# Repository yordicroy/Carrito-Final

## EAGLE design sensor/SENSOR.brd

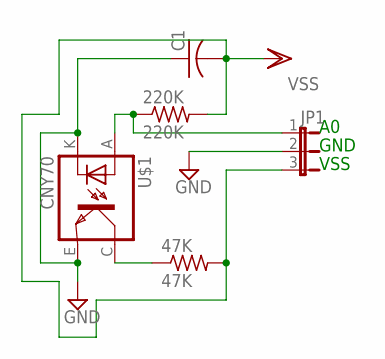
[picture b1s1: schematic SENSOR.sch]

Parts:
47K: 47K; 0309/12
220K: 220K; 0309/12
C1: C-US025-030X050; C025-030X050
JP1: JP2E; JP2
U$1: CNY70; 4

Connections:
GND: C1.1, JP1.2, U$1.E (EMI), U$1.K (C)
unnamed: 220K.1, JP1.1, U$1.A
unnamed: 47K.1, U$1.C (COL)
VSS: 47K.2, 220K.2, C1.2, JP1.3

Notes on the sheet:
GND
VSS

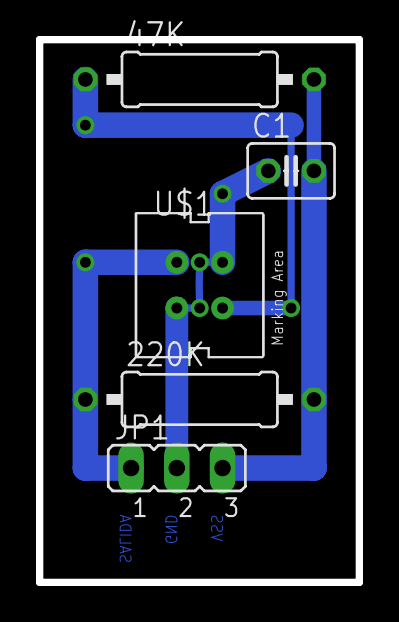
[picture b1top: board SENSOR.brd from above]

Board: 2 copper layers, 17.8 x 30.2 mm, 5 parts (0 on the bottom side), 4 nets.

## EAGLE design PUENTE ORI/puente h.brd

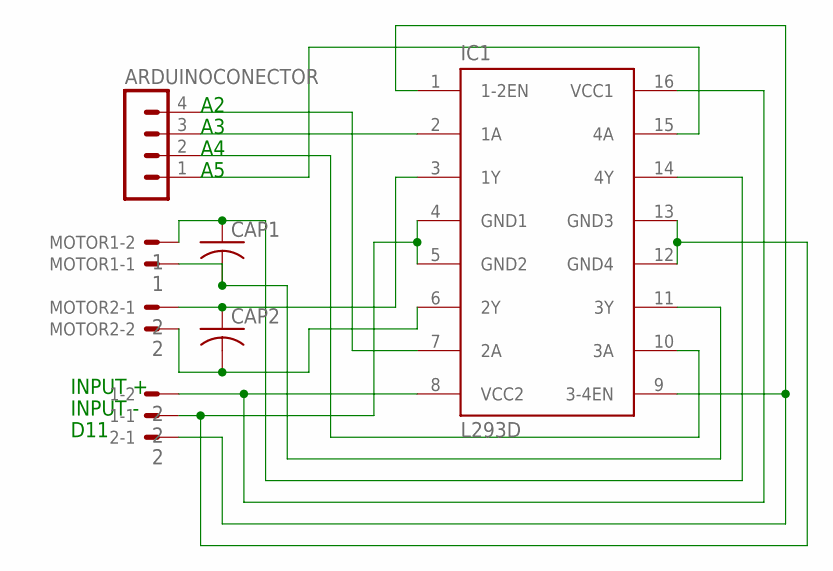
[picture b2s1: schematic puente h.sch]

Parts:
1, 2: 2; 332-02
ARDUINOCONECTOR: MA04-1
CAP1, CAP2: C-US025-025X050; C025-025X050
IC1: L293D; DIL16
MOTOR1: 1; 332-02
MOTOR2: 2; 332-02

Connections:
unnamed: ARDUINOCONECTOR.4, IC1.7 (2A)
unnamed: ARDUINOCONECTOR.3, IC1.2 (1A)
unnamed: ARDUINOCONECTOR.2, IC1.10 (3A)
unnamed: ARDUINOCONECTOR.1, IC1.15 (4A)
unnamed: CAP1.2, IC1.11 (3Y), MOTOR1.1
unnamed: CAP1.1, IC1.14 (4Y), MOTOR1.2
unnamed: 1.2, IC1.8 (VCC2), IC1.16 (VCC1)
unnamed: CAP2.1, IC1.3 (1Y), MOTOR2.1
unnamed: CAP2.2, IC1.6 (2Y), MOTOR2.2
unnamed: 2.1, IC1.1 (1-2EN), IC1.9 (3-4EN)
unnamed: 1.1, IC1.4 (GND1), IC1.5 (GND2), IC1.12 (GND4), IC1.13 (GND3)

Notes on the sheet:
INPUT +
INPUT -
D11

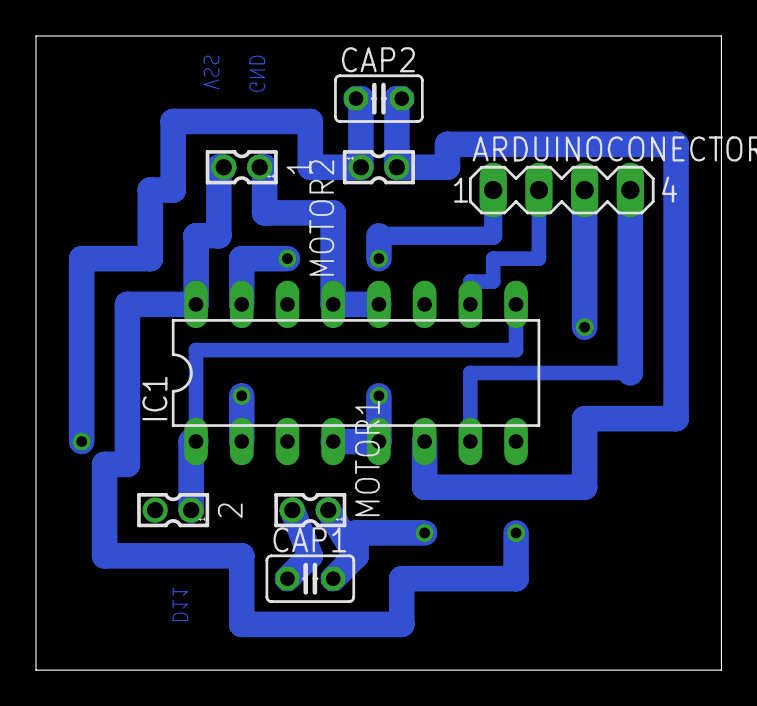
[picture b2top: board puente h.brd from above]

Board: 2 copper layers, 38.1 x 35.2 mm, 8 parts (0 on the bottom side), 11 nets.

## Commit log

2018-06-13 Documento IEEE FINAL
2018-06-13 PUENTE ORI
2018-06-13 Codigo del Seguidor de linea
2018-06-13 SENSOR
